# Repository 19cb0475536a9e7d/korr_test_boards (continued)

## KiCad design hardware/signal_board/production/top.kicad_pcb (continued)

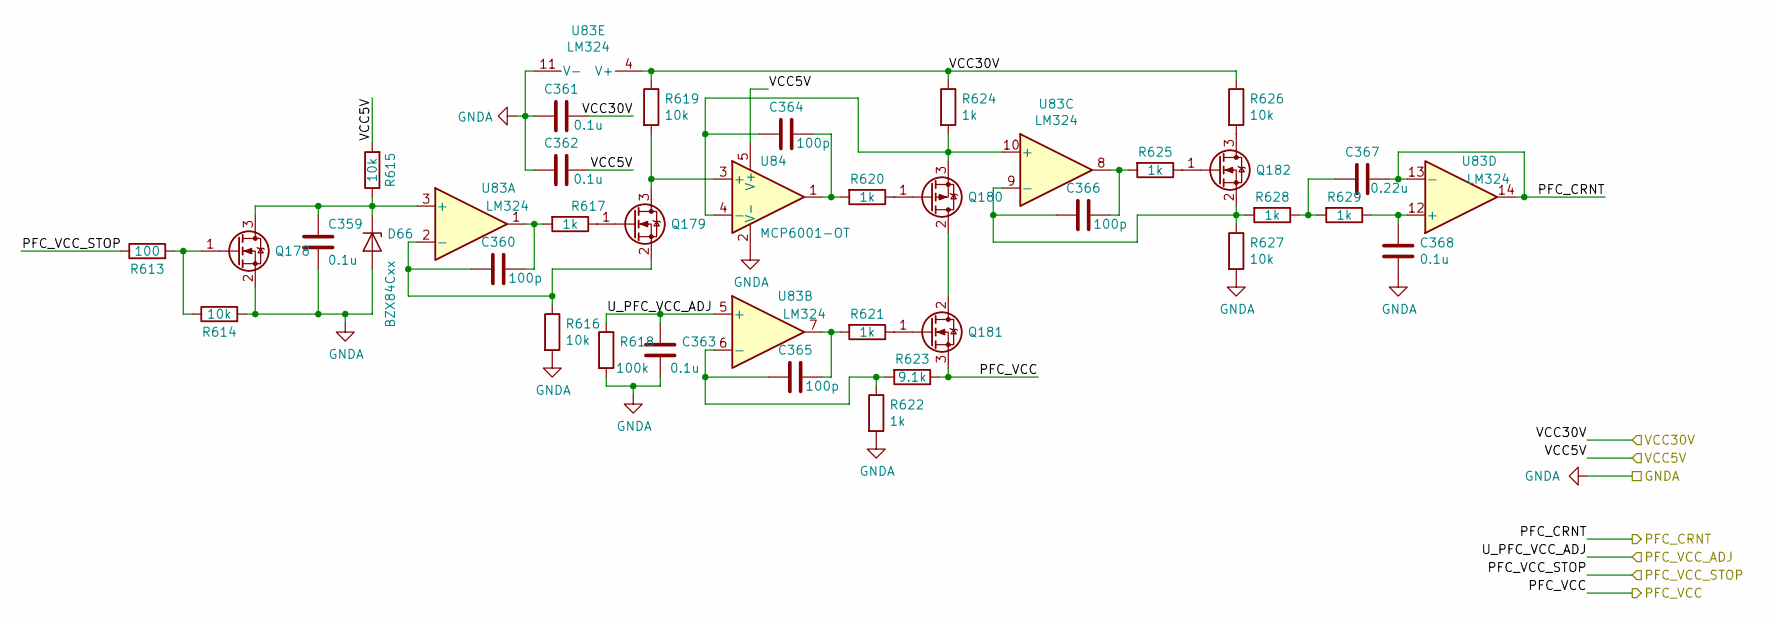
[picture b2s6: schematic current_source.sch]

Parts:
C12, C14, C15, C16, C21: 0.1u; C_0603_1608Metric
C13, C17, C18, C19: 100p; C_0603_1608Metric
C20: 0.22u; C_0603_1608Metric
D2: BZX84Cxx; D_SOT-23_ANK
Q8, Q9, Q12: Q_NMOS_GSD; SOT-23
Q10: Q_PMOS_GDS; TO-252-2
Q11: Q_NMOS_GDS; TO-252-2
R24: 100; R_0603_1608Metric
R25, R26, R27, R30, R37, R38: 10k; R_0603_1608Metric
R28, R31, R32, R33, R36, R39, R40: 1k; R_0603_1608Metric
R29: 100k; R_0603_1608Metric
R34: 9.1k; R_0603_1608Metric
R35: 1k; R_1206_3216Metric
U4: LM324; SOIC-14_3.9x8.7mm_P1.27mm
U5: MCP6001-OT; SOT-23-5

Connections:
/Cell_0_Sheet/CurrentSource_A_Sheet/PFC_CRNT: C20.1, U4.13 (-), U4.14; also elsewhere on the board
/PFC_STOP_0: R24.1; also elsewhere on the board
/PFC_VCC_DUT_0: Q11.3 (S), R34.1; also elsewhere on the board
/U_PFC_VCC_ADJ: C16.1, R29.1, U4.5 (+); also elsewhere on the board
/VCC5V: C15.1, R26.2, U5.5 (V+); also elsewhere on the board
/VCC30V: C14.1, R30.1, R35.1, R37.1, U4.4 (V+); also elsewhere on the board
GNDA: C12.2, C14.2, C15.2, C16.2, C21.2, D2.2 (A), Q8.2 (S), R25.2, R27.2, R29.2, R33.2, R38.2, U4.11 (V-), U5.2 (V-); also elsewhere on the board
unnamed: C12.1, D2.1 (K), Q8.3 (D), R26.1, U4.3 (+)
unnamed: C13.1, R28.2, U4.1
unnamed: C13.2, Q9.2 (S), R27.1, U4.2 (-)
unnamed: C17.1, R31.2, U5.1
unnamed: C17.2, Q10.3 (S), R35.2, U4.10 (+), U5.4 (-)
unnamed: C18.1, R32.2, U4.7
unnamed: C18.2, R33.1, R34.2, U4.6 (-)
unnamed: C19.1, R36.2, U4.8
unnamed: C19.2, Q12.2 (S), R38.1, R39.2, U4.9 (-)
unnamed: C20.2, R39.1, R40.2
unnamed: C21.1, R40.1, U4.12 (+)
unnamed: Q8.1 (G), R24.2, R25.1
unnamed: Q9.1 (G), R28.1
unnamed: Q9.3 (D), R30.2, U5.3 (+)
unnamed: Q10.1 (G), R31.1
unnamed: Q10.2 (D), Q11.2 (D)
unnamed: Q11.1 (G), R32.1
unnamed: Q12.1 (G), R36.1
unnamed: Q12.3 (D), R37.2

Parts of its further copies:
C2, C4, C5, C6, C11, C39, C41, C42, C43, C48, C49, C51, C52, C53, C58, C63, C65, C66, C67, C72, C73, C109, C110, C111, C116, C118, C120, C121, C122, C127, C128, C130, C131, C132, C137, C139, C141, C142, C143, C148, C149, C151, C152, C153, C158, C160, C162, C163, C164, C169, C170, C172, C173, C174, C179, C181, C183, C184, C185, C190, C191, C193, C194, C195, C200, C202, C204, C205, C206, C211, C212, C214, C215, C216, C221, C223, C225, C226, C227, C232, C233, C235, C236, C237, C242, C244, C246, C247, C248, C253, C254, C256, C257, C258, C263, C265, C267, C268, C269, C274, C275, C277, C278, C279, C284, C286, C288, C289, C290, C295, C296, C298, C299, C300, C305, C307, C309, C310, C311, C316, C317, C319, C320, C321, C326, C328, C330, C331, C332, C337, C338, C340, C341, C342, C347, C349, C351, C352, C353, C358, C359, C361, C362, C363, C368: 0.1u; C_0603_1608Metric
C3, C7, C8, C9, C40, C44, C45, C46, C50, C54, C55, C56, C64, C68, C69, C70, C108, C112, C113, C114, C119, C123, C124, C125, C129, C133, C134, C135, C140, C144, C145, C146, C150, C154, C155, C156, C161, C165, C166, C167, C171, C175, C176, C177, C182, C186, C187, C188, C192, C196, C197, C198, C203, C207, C208, C209, C213, C217, C218, C219, C224, C228, C229, C230, C234, C238, C239, C240, C245, C249, C250, C251, C255, C259, C260, C261, C266, C270, C271, C272, C276, C280, C281, C282, C287, C291, C292, C293, C297, C301, C302, C303, C308, C312, C313, C314, C318, C322, C323, C324, C329, C333, C334, C335, C339, C343, C344, C345, C350, C354, C355, C356, C360, C364, C365, C366: 100p; C_0603_1608Metric
C10, C47, C57, C71, C115, C126, C136, C147, C157, C168, C178, C189, C199, C210, C220, C231, C241, C252, C262, C273, C283, C294, C304, C315, C325, C336, C346, C357, C367: 0.22u; C_0603_1608Metric
D1, D5, D6, D41, D42, D43, D44, D45, D46, D47, D48, D49, D50, D51, D52, D53, D54, D55, D56, D57, D58, D59, D60, D61, D62, D63, D64, D65, D66: BZX84Cxx; D_SOT-23_ANK
Q3, Q4, Q7, Q16, Q17, Q20, Q21, Q22, Q25, Q29, Q30, Q33, Q34, Q35, Q38, Q41, Q42, Q45, Q46, Q47, Q50, Q53, Q54, Q57, Q58, Q59, Q62, Q65, Q66, Q69, Q70, Q71, Q74, Q77, Q78, Q81, Q82, Q83, Q86, Q89, Q90, Q93, Q94, Q95, Q98, Q101, Q102, Q105, Q106, Q107, Q110, Q113, Q114, Q117, Q118, Q119, Q122, Q125, Q126, Q129, Q130, Q131, Q134, Q137, Q138, Q141, Q142, Q143, Q146, Q149, Q150, Q153, Q154, Q155, Q158, Q161, Q162, Q165, Q166, Q167, Q170, Q173, Q174, Q177, Q178, Q179, Q182: Q_NMOS_GSD; SOT-23
Q5, Q18, Q23, Q31, Q36, Q43, Q48, Q55, Q60, Q67, Q72, Q79, Q84, Q91, Q96, Q103, Q108, Q115, Q120, Q127, Q132, Q139, Q144, Q151, Q156, Q163, Q168, Q175, Q180: Q_PMOS_GDS; TO-252-2
Q6, Q19, Q24, Q32, Q37, Q44, Q49, Q56, Q61, Q68, Q73, Q80, Q85, Q92, Q97, Q104, Q109, Q116, Q121, Q128, Q133, Q140, Q145, Q152, Q157, Q164, Q169, Q176, Q181: Q_NMOS_GDS; TO-252-2
R7, R59, R76, R106, R133, R156, R173, R196, R213, R236, R253, R276, R293, R316, R333, R356, R373, R396, R413, R436, R453, R476, R493, R516, R533, R556, R573, R596, R613: 100; R_0603_1608Metric
R8, R9, R10, R13, R20, R21, R60, R61, R62, R65, R72, R73, R77, R78, R79, R82, R89, R90, R107, R118, R119, R122, R129, R130, R134, R135, R136, R139, R146, R147, R157, R158, R159, R162, R169, R170, R174, R175, R176, R179, R186, R187, R197, R198, R199, R202, R209, R210, R214, R215, R216, R219, R226, R227, R237, R238, R239, R242, R249, R250, R254, R255, R256, R259, R266, R267, R277, R278, R279, R282, R289, R290, R294, R295, R296, R299, R306, R307, R317, R318, R319, R322, R329, R330, R334, R335, R336, R339, R346, R347, R357, R358, R359, R362, R369, R370, R374, R375, R376, R379, R386, R387, R397, R398, R399, R402, R409, R410, R414, R415, R416, R419, R426, R427, R437, R438, R439, R442, R449, R450, R454, R455, R456, R459, R466, R467, R477, R478, R479, R482, R489, R490, R494, R495, R496, R499, R506, R507, R517, R518, R519, R522, R529, R530, R534, R535, R536, R539, R546, R547, R557, R558, R559, R562, R569, R570, R574, R575, R576, R579, R586, R587, R597, R598, R599, R602, R609, R610, R614, R615, R616, R619, R626, R627: 10k; R_0603_1608Metric
R11, R14, R15, R16, R19, R22, R23, R63, R66, R67, R68, R71, R74, R75, R80, R83, R84, R85, R88, R91, R92, R120, R123, R124, R125, R128, R131, R132, R137, R140, R141, R142, R145, R148, R149, R160, R163, R164, R165, R168, R171, R172, R177, R180, R181, R182, R185, R188, R189, R200, R203, R204, R205, R208, R211, R212, R217, R220, R221, R222, R225, R228, R229, R240, R243, R244, R245, R248, R251, R252, R257, R260, R261, R262, R265, R268, R269, R280, R283, R284, R285, R288, R291, R292, R297, R300, R301, R302, R305, R308, R309, R320, R323, R324, R325, R328, R331, R332, R337, R340, R341, R342, R345, R348, R349, R360, R363, R364, R365, R368, R371, R372, R377, R380, R381, R382, R385, R388, R389, R400, R403, R404, R405, R408, R411, R412, R417, R420, R421, R422, R425, R428, R429, R440, R443, R444, R445, R448, R451, R452, R457, R460, R461, R462, R465, R468, R469, R480, R483, R484, R485, R488, R491, R492, R497, R500, R501, R502, R505, R508, R509, R520, R523, R524, R525, R528, R531, R532, R537, R540, R541, R542, R545, R548, R549, R560, R563, R564, R565, R568, R571, R572, R577, R580, R581, R582, R585, R588, R589, R600, R603, R604, R605, R608, R611, R612, R617, R620, R621, R622, R625, R628, R629: 1k; R_0603_1608Metric
R12, R64, R81, R121, R138, R161, R178, R201, R218, R241, R258, R281, R298, R321, R338, R361, R378, R401, R418, R441, R458, R481, R498, R521, R538, R561, R578, R601, R618: 100k; R_0603_1608Metric
R17, R69, R86, R126, R143, R166, R183, R206, R223, R246, R263, R286, R303, R326, R343, R366, R383, R406, R423, R446, R463, R486, R503, R526, R543, R566, R583, R606, R623: 9.1k; R_0603_1608Metric
R18, R70, R87, R127, R144, R167, R184, R207, R224, R247, R264, R287, R304, R327, R344, R367, R384, R407, R424, R447, R464, R487, R504, R527, R544, R567, R584, R607, R624: 1k; R_1206_3216Metric
U2, U11, U13, U17, U19, U26, U28, U31, U33, U36, U38, U41, U43, U46, U48, U51, U53, U56, U58, U61, U63, U66, U68, U71, U73, U76, U78, U81, U83: LM324; SOIC-14_3.9x8.7mm_P1.27mm
U3, U12, U14, U18, U24, U27, U29, U32, U34, U37, U39, U42, U44, U47, U49, U52, U54, U57, U59, U62, U64, U67, U69, U72, U74, U77, U79, U82, U84: MCP6001-OT; SOT-23-5

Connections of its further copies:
/Cell_0_Sheet/CurrentSource_B_Sheet/PFC_CRNT: C10.1, U2.13 (-), U2.14; also elsewhere on the board
/Cell_1_Sheet/CurrentSource_A_Sheet/PFC_CRNT: C57.1, U13.13 (-), U13.14; also elsewhere on the board
/Cell_1_Sheet/CurrentSource_B_Sheet/PFC_CRNT: C47.1, U11.13 (-), U11.14; also elsewhere on the board
/Cell_2_Sheet/CurrentSource_A_Sheet/PFC_CRNT: C115.1, U19.13 (-), U19.14; also elsewhere on the board
/Cell_2_Sheet/CurrentSource_B_Sheet/PFC_CRNT: C71.1, U17.13 (-), U17.14; also elsewhere on the board
/Cell_3_Sheet/CurrentSource_A_Sheet/PFC_CRNT: C136.1, U28.13 (-), U28.14; also elsewhere on the board
/Cell_3_Sheet/CurrentSource_B_Sheet/PFC_CRNT: C126.1, U26.13 (-), U26.14; also elsewhere on the board
/PFC_STOP_1: R7.1; also elsewhere on the board
/PFC_STOP_2: R76.1; also elsewhere on the board
/PFC_STOP_3: R59.1; also elsewhere on the board
/PFC_STOP_4: R133.1; also elsewhere on the board
/PFC_STOP_5: R106.1; also elsewhere on the board
/PFC_STOP_6: R173.1; also elsewhere on the board
/PFC_STOP_7: R156.1; also elsewhere on the board
/PFC_STOP_8: R213.1; also elsewhere on the board
/PFC_STOP_9: R196.1; also elsewhere on the board
/PFC_STOP_10: R253.1; also elsewhere on the board
/PFC_STOP_11: R236.1; also elsewhere on the board
/PFC_STOP_12: R293.1; also elsewhere on the board
/PFC_STOP_13: R276.1; also elsewhere on the board
/PFC_STOP_14: R333.1; also elsewhere on the board
/PFC_STOP_15: R316.1; also elsewhere on the board
/PFC_STOP_16: R373.1; also elsewhere on the board
/PFC_STOP_17: R356.1; also elsewhere on the board
/PFC_STOP_18: R413.1; also elsewhere on the board
/PFC_STOP_19: R396.1; also elsewhere on the board
/PFC_STOP_20: R453.1; also elsewhere on the board
/PFC_STOP_21: R436.1; also elsewhere on the board
/PFC_STOP_22: R493.1; also elsewhere on the board
/PFC_STOP_23: R476.1; also elsewhere on the board
/PFC_STOP_24: R533.1; also elsewhere on the board
/PFC_STOP_25: R516.1; also elsewhere on the board
/PFC_STOP_26: R573.1; also elsewhere on the board
/PFC_STOP_27: R556.1; also elsewhere on the board
/PFC_STOP_28: R613.1; also elsewhere on the board
/PFC_STOP_29: R596.1; also elsewhere on the board
/PFC_VCC_DUT_1: Q6.3 (S), R17.1; also elsewhere on the board
/PFC_VCC_DUT_2: Q24.3 (S), R86.1; also elsewhere on the board
/PFC_VCC_DUT_3: Q19.3 (S), R69.1; also elsewhere on the board
/PFC_VCC_DUT_4: Q37.3 (S), R143.1; also elsewhere on the board
/PFC_VCC_DUT_5: Q32.3 (S), R126.1; also elsewhere on the board
/PFC_VCC_DUT_6: Q49.3 (S), R183.1; also elsewhere on the board
/PFC_VCC_DUT_7: Q44.3 (S), R166.1; also elsewhere on the board
/PFC_VCC_DUT_8: Q61.3 (S), R223.1; also elsewhere on the board
/PFC_VCC_DUT_9: Q56.3 (S), R206.1; also elsewhere on the board
/PFC_VCC_DUT_10: Q73.3 (S), R263.1; also elsewhere on the board
/PFC_VCC_DUT_11: Q68.3 (S), R246.1; also elsewhere on the board
/PFC_VCC_DUT_12: Q85.3 (S), R303.1; also elsewhere on the board
/PFC_VCC_DUT_13: Q80.3 (S), R286.1; also elsewhere on the board
/PFC_VCC_DUT_14: Q97.3 (S), R343.1; also elsewhere on the board
/PFC_VCC_DUT_15: Q92.3 (S), R326.1; also elsewhere on the board
/PFC_VCC_DUT_16: Q109.3 (S), R383.1; also elsewhere on the board
/PFC_VCC_DUT_17: Q104.3 (S), R366.1; also elsewhere on the board
/PFC_VCC_DUT_18: Q121.3 (S), R423.1; also elsewhere on the board
/PFC_VCC_DUT_19: Q116.3 (S), R406.1; also elsewhere on the board
/PFC_VCC_DUT_20: Q133.3 (S), R463.1; also elsewhere on the board
/PFC_VCC_DUT_21: Q128.3 (S), R446.1; also elsewhere on the board
/PFC_VCC_DUT_22: Q145.3 (S), R503.1; also elsewhere on the board
/PFC_VCC_DUT_23: Q140.3 (S), R486.1; also elsewhere on the board
/PFC_VCC_DUT_24: Q157.3 (S), R543.1; also elsewhere on the board
/PFC_VCC_DUT_25: Q152.3 (S), R526.1; also elsewhere on the board
/PFC_VCC_DUT_26: Q169.3 (S), R583.1; also elsewhere on the board
/PFC_VCC_DUT_27: Q164.3 (S), R566.1; also elsewhere on the board
/PFC_VCC_DUT_28: Q181.3 (S), R623.1; also elsewhere on the board
/PFC_VCC_DUT_29: Q176.3 (S), R606.1; also elsewhere on the board
/U_PFC_VCC_ADJ: C6.1, C43.1, C53.1, C67.1, C111.1, C122.1, C132.1, C143.1, C153.1, C164.1, C174.1, C185.1, C195.1, C206.1, C216.1, C227.1, C237.1, C248.1, C258.1, C269.1, C279.1, C290.1, C300.1, C311.1, C321.1, C332.1, C342.1, C353.1, C363.1, R12.1, R64.1, R81.1, R121.1, R138.1, R161.1, R178.1, R201.1, R218.1, R241.1, R258.1, R281.1, R298.1, R321.1, R338.1, R361.1, R378.1, R401.1, R418.1, R441.1, R458.1, R481.1, R498.1, R521.1, R538.1, R561.1, R578.1, R601.1, R618.1, U2.5 (+), U11.5 (+), U13.5 (+), U17.5 (+), U19.5 (+), U26.5 (+), U28.5 (+), U31.5 (+), U33.5 (+), U36.5 (+), U38.5 (+), U41.5 (+), U43.5 (+), U46.5 (+), U48.5 (+), U51.5 (+), U53.5 (+), U56.5 (+), U58.5 (+), U61.5 (+), U63.5 (+), U66.5 (+), U68.5 (+), U71.5 (+), U73.5 (+), U76.5 (+), U78.5 (+), U81.5 (+), U83.5 (+); also elsewhere on the board
/VCC5V: C5.1, C42.1, C52.1, C66.1, C110.1, C121.1, C131.1, C142.1, C152.1, C163.1, C173.1, C184.1, C194.1, C205.1, C215.1, C226.1, C236.1, C247.1, C257.1, C268.1, C278.1, C289.1, C299.1, C310.1, C320.1, C331.1, C341.1, C352.1, C362.1, R9.2, R61.2, R78.2, R118.2, R135.2, R158.2, R175.2, R198.2, R215.2, R238.2, R255.2, R278.2, R295.2, R318.2, R335.2, R358.2, R375.2, R398.2, R415.2, R438.2, R455.2, R478.2, R495.2, R518.2, R535.2, R558.2, R575.2, R598.2, R615.2, U3.5 (V+), U12.5 (V+), U14.5 (V+), U18.5 (V+), U24.5 (V+), U27.5 (V+), U29.5 (V+), U32.5 (V+), U34.5 (V+), U37.5 (V+), U39.5 (V+), U42.5 (V+), U44.5 (V+), U47.5 (V+), U49.5 (V+), U52.5 (V+), U54.5 (V+), U57.5 (V+), U59.5 (V+), U62.5 (V+), U64.5 (V+), U67.5 (V+), U69.5 (V+), U72.5 (V+), U74.5 (V+), U77.5 (V+), U79.5 (V+), U82.5 (V+), U84.5 (V+); also elsewhere on the board
/VCC30V: C4.1, C41.1, C51.1, C65.1, C109.1, C120.1, C130.1, C141.1, C151.1, C162.1, C172.1, C183.1, C193.1, C204.1, C214.1, C225.1, C235.1, C246.1, C256.1, C267.1, C277.1, C288.1, C298.1, C309.1, C319.1, C330.1, C340.1, C351.1, C361.1, R13.1, R18.1, R20.1, R65.1, R70.1, R72.1, R82.1, R87.1, R89.1, R122.1, R127.1, R129.1, R139.1, R144.1, R146.1, R162.1, R167.1, R169.1, R179.1, R184.1, R186.1, R202.1, R207.1, R209.1, R219.1, R224.1, R226.1, R242.1, R247.1, R249.1, R259.1, R264.1, R266.1, R282.1, R287.1, R289.1, R299.1, R304.1, R306.1, R322.1, R327.1, R329.1, R339.1, R344.1, R346.1, R362.1, R367.1, R369.1, R379.1, R384.1, R386.1, R402.1, R407.1, R409.1, R419.1, R424.1, R426.1, R442.1, R447.1, R449.1, R459.1, R464.1, R466.1, R482.1, R487.1, R489.1, R499.1, R504.1, R506.1, R522.1, R527.1, R529.1, R539.1, R544.1, R546.1, R562.1, R567.1, R569.1, R579.1, R584.1, R586.1, R602.1, R607.1, R609.1, R619.1, R624.1, R626.1, U2.4 (V+), U11.4 (V+), U13.4 (V+), U17.4 (V+), U19.4 (V+), U26.4 (V+), U28.4 (V+), U31.4 (V+), U33.4 (V+), U36.4 (V+), U38.4 (V+), U41.4 (V+), U43.4 (V+), U46.4 (V+), U48.4 (V+), U51.4 (V+), U53.4 (V+), U56.4 (V+), U58.4 (V+), U61.4 (V+), U63.4 (V+), U66.4 (V+), U68.4 (V+), U71.4 (V+), U73.4 (V+), U76.4 (V+), U78.4 (V+), U81.4 (V+), U83.4 (V+); also elsewhere on the board
/sheet5E9AFF1E/CurrentSource_A_Sheet/PFC_CRNT: C283.1, U63.13 (-), U63.14; also elsewhere on the board
/sheet5E9AFF1E/CurrentSource_B_Sheet/PFC_CRNT: C273.1, U61.13 (-), U61.14; also elsewhere on the board
/sheet5E9AFF1F/CurrentSource_A_Sheet/PFC_CRNT: C304.1, U68.13 (-), U68.14; also elsewhere on the board
/sheet5E9AFF1F/CurrentSource_B_Sheet/PFC_CRNT: C294.1, U66.13 (-), U66.14; also elsewhere on the board
/sheet5E9AFF20/CurrentSource_A_Sheet/PFC_CRNT: C325.1, U73.13 (-), U73.14; also elsewhere on the board
/sheet5E9AFF20/CurrentSource_B_Sheet/PFC_CRNT: C315.1, U71.13 (-), U71.14; also elsewhere on the board
/sheet5E9AFF21/CurrentSource_A_Sheet/PFC_CRNT: C346.1, U78.13 (-), U78.14; also elsewhere on the board
/sheet5E9AFF21/CurrentSource_B_Sheet/PFC_CRNT: C336.1, U76.13 (-), U76.14; also elsewhere on the board
/sheet5E9AFF22/CurrentSource_A_Sheet/PFC_CRNT: C367.1, U83.13 (-), U83.14; also elsewhere on the board
/sheet5E9AFF22/CurrentSource_B_Sheet/PFC_CRNT: C357.1, U81.13 (-), U81.14; also elsewhere on the board
/sheet5E8790F9/CurrentSource_A_Sheet/PFC_CRNT: C157.1, U33.13 (-), U33.14; also elsewhere on the board
/sheet5E8790F9/CurrentSource_B_Sheet/PFC_CRNT: C147.1, U31.13 (-), U31.14; also elsewhere on the board
/sheet5E9528FB/CurrentSource_A_Sheet/PFC_CRNT: C178.1, U38.13 (-), U38.14; also elsewhere on the board
/sheet5E9528FB/CurrentSource_B_Sheet/PFC_CRNT: C168.1, U36.13 (-), U36.14; also elsewhere on the board
/sheet5E9528FC/CurrentSource_A_Sheet/PFC_CRNT: C199.1, U43.13 (-), U43.14; also elsewhere on the board
/sheet5E9528FC/CurrentSource_B_Sheet/PFC_CRNT: C189.1, U41.13 (-), U41.14; also elsewhere on the board
/sheet5E9528FD/CurrentSource_A_Sheet/PFC_CRNT: C220.1, U48.13 (-), U48.14; also elsewhere on the board
/sheet5E9528FD/CurrentSource_B_Sheet/PFC_CRNT: C210.1, U46.13 (-), U46.14; also elsewhere on the board
/sheet5E9528FE/CurrentSource_A_Sheet/PFC_CRNT: C241.1, U53.13 (-), U53.14; also elsewhere on the board
/sheet5E9528FE/CurrentSource_B_Sheet/PFC_CRNT: C231.1, U51.13 (-), U51.14; also elsewhere on the board
/sheet5E9528FF/CurrentSource_A_Sheet/PFC_CRNT: C262.1, U58.13 (-), U58.14; also elsewhere on the board
/sheet5E9528FF/CurrentSource_B_Sheet/PFC_CRNT: C252.1, U56.13 (-), U56.14; also elsewhere on the board
GNDA: C2.2, C4.2, C5.2, C6.2, C11.2, C39.2, C41.2, C42.2, C43.2, C48.2, C49.2, C51.2, C52.2, C53.2, C58.2, C63.2, C65.2, C66.2, C67.2, C72.2, C73.2, C109.2, C110.2, C111.2, C116.2, C118.2, C120.2, C121.2, C122.2, C127.2, C128.2, C130.2, C131.2, C132.2, C137.2, C139.2, C141.2, C142.2, C143.2, C148.2, C149.2, C151.2, C152.2, C153.2, C158.2, C160.2, C162.2, C163.2, C164.2, C169.2, C170.2, C172.2, C173.2, C174.2, C179.2, C181.2, C183.2, C184.2, C185.2, C190.2, C191.2, C193.2, C194.2, C195.2, C200.2, C202.2, C204.2, C205.2, C206.2, C211.2, C212.2, C214.2, C215.2, C216.2, C221.2, C223.2, C225.2, C226.2, C227.2, C232.2, C233.2, C235.2, C236.2, C237.2, C242.2, C244.2, C246.2, C247.2, C248.2, C253.2, C254.2, C256.2, C257.2, C258.2, C263.2, C265.2, C267.2, C268.2, C269.2, C274.2, C275.2, C277.2, C278.2, C279.2, C284.2, C286.2, C288.2, C289.2, C290.2, C295.2, C296.2, C298.2, C299.2, C300.2, C305.2, C307.2, C309.2, C310.2, C311.2, C316.2, C317.2, C319.2, C320.2, C321.2, C326.2, C328.2, C330.2, C331.2, C332.2, C337.2, C338.2, C340.2, C341.2, C342.2, C347.2, C349.2, C351.2, C352.2, C353.2, C358.2, C359.2, C361.2, C362.2, C363.2, C368.2, D1.2 (A), D5.2 (A), D6.2 (A), D41.2 (A), D42.2 (A), D43.2 (A), D44.2 (A), D45.2 (A), D46.2 (A), D47.2 (A), D48.2 (A), D49.2 (A), D50.2 (A), D51.2 (A), D52.2 (A), D53.2 (A), D54.2 (A), D55.2 (A), D56.2 (A), D57.2 (A), D58.2 (A), D59.2 (A), D60.2 (A), D61.2 (A), D62.2 (A), D63.2 (A), D64.2 (A), D65.2 (A), D66.2 (A), Q3.2 (S), Q16.2 (S), Q21.2 (S), Q29.2 (S), Q34.2 (S), Q41.2 (S), Q46.2 (S), Q53.2 (S), Q58.2 (S), Q65.2 (S), Q70.2 (S), Q77.2 (S), Q82.2 (S), Q89.2 (S), Q94.2 (S), Q101.2 (S), Q106.2 (S), Q113.2 (S), Q118.2 (S), Q125.2 (S), Q130.2 (S), Q137.2 (S), Q142.2 (S), Q149.2 (S), Q154.2 (S), Q161.2 (S), Q166.2 (S), Q173.2 (S), Q178.2 (S), R8.2, R10.2, R12.2, R16.2, R21.2, R60.2, R62.2, R64.2, R68.2, R73.2, R77.2, R79.2, R81.2, R85.2, R90.2, R107.2, R119.2, R121.2, R125.2, R130.2, R134.2, R136.2, R138.2, R142.2, R147.2, R157.2, R159.2, R161.2, R165.2, R170.2, R174.2, R176.2, R178.2, R182.2, R187.2, R197.2, R199.2, R201.2, R205.2, R210.2, R214.2, R216.2, R218.2, R222.2, R227.2, R237.2, R239.2, R241.2, R245.2, R250.2, R254.2, R256.2, R258.2, R262.2, R267.2, R277.2, R279.2, R281.2, R285.2, R290.2, R294.2, R296.2, R298.2, R302.2, R307.2, R317.2, R319.2, R321.2, R325.2, R330.2, R334.2, R336.2, R338.2, R342.2, R347.2, R357.2, R359.2, R361.2, R365.2, R370.2, R374.2, R376.2, R378.2, R382.2, R387.2, R397.2, R399.2, R401.2, R405.2, R410.2, R414.2, R416.2, R418.2, R422.2, R427.2, R437.2, R439.2, R441.2, R445.2, R450.2, R454.2, R456.2, R458.2, R462.2, R467.2, R477.2, R479.2, R481.2, R485.2, R490.2, R494.2, R496.2, R498.2, R502.2, R507.2, R517.2, R519.2, R521.2, R525.2, R530.2, R534.2, R536.2, R538.2, R542.2, R547.2, R557.2, R559.2, R561.2, R565.2, R570.2, R574.2, R576.2, R578.2, R582.2, R587.2, R597.2, R599.2, R601.2, R605.2, R610.2, R614.2, R616.2, R618.2, R622.2, R627.2, U2.11 (V-), U3.2 (V-), U11.11 (V-), U12.2 (V-), U13.11 (V-), U14.2 (V-), U17.11 (V-), U18.2 (V-), U19.11 (V-), U24.2 (V-), U26.11 (V-), U27.2 (V-), U28.11 (V-), U29.2 (V-), U31.11 (V-), U32.2 (V-), U33.11 (V-), U34.2 (V-), U36.11 (V-), U37.2 (V-), U38.11 (V-), U39.2 (V-), U41.11 (V-), U42.2 (V-), U43.11 (V-), U44.2 (V-), U46.11 (V-), U47.2 (V-), U48.11 (V-), U49.2 (V-), U51.11 (V-), U52.2 (V-), U53.11 (V-), U54.2 (V-), U56.11 (V-), U57.2 (V-), U58.11 (V-), U59.2 (V-), U61.11 (V-), U62.2 (V-), U63.11 (V-), U64.2 (V-), U66.11 (V-), U67.2 (V-), U68.11 (V-), U69.2 (V-), U71.11 (V-), U72.2 (V-), U73.11 (V-), U74.2 (V-), U76.11 (V-), U77.2 (V-), U78.11 (V-), U79.2 (V-), U81.11 (V-), U82.2 (V-), U83.11 (V-), U84.2 (V-); also elsewhere on the board
unnamed: C2.1, D1.1 (K), Q3.3 (D), R9.1, U2.3 (+)
unnamed: C3.1, R11.2, U2.1
unnamed: C3.2, Q4.2 (S), R10.1, U2.2 (-)
unnamed: C7.1, R14.2, U3.1
unnamed: C7.2, Q5.3 (S), R18.2, U2.10 (+), U3.4 (-)
unnamed: C8.1, R15.2, U2.7
unnamed: C8.2, R16.1, R17.2, U2.6 (-)
unnamed: C9.1, R19.2, U2.8
unnamed: C9.2, Q7.2 (S), R21.1, R22.2, U2.9 (-)
unnamed: C10.2, R22.1, R23.2
unnamed: C11.1, R23.1, U2.12 (+)
unnamed: C39.1, D5.1 (K), Q16.3 (D), R61.1, U11.3 (+)
unnamed: C40.1, R63.2, U11.1
unnamed: C40.2, Q17.2 (S), R62.1, U11.2 (-)
unnamed: C44.1, R66.2, U12.1
unnamed: C44.2, Q18.3 (S), R70.2, U11.10 (+), U12.4 (-)
unnamed: C45.1, R67.2, U11.7
unnamed: C45.2, R68.1, R69.2, U11.6 (-)
unnamed: C46.1, R71.2, U11.8
unnamed: C46.2, Q20.2 (S), R73.1, R74.2, U11.9 (-)
unnamed: C47.2, R74.1, R75.2
unnamed: C48.1, R75.1, U11.12 (+)
unnamed: C49.1, D6.1 (K), Q21.3 (D), R78.1, U13.3 (+)
unnamed: C50.1, R80.2, U13.1
unnamed: C50.2, Q22.2 (S), R79.1, U13.2 (-)
unnamed: C54.1, R83.2, U14.1
unnamed: C54.2, Q23.3 (S), R87.2, U13.10 (+), U14.4 (-)
unnamed: C55.1, R84.2, U13.7
unnamed: C55.2, R85.1, R86.2, U13.6 (-)
unnamed: C56.1, R88.2, U13.8
unnamed: C56.2, Q25.2 (S), R90.1, R91.2, U13.9 (-)
unnamed: C57.2, R91.1, R92.2
unnamed: C58.1, R92.1, U13.12 (+)
unnamed: C63.1, D41.1 (K), Q29.3 (D), R118.1, U17.3 (+)
unnamed: C64.1, R120.2, U17.1
unnamed: C64.2, Q30.2 (S), R119.1, U17.2 (-)
unnamed: C68.1, R123.2, U18.1
unnamed: C68.2, Q31.3 (S), R127.2, U17.10 (+), U18.4 (-)
unnamed: C69.1, R124.2, U17.7
unnamed: C69.2, R125.1, R126.2, U17.6 (-)
unnamed: C70.1, R128.2, U17.8
unnamed: C70.2, Q33.2 (S), R130.1, R131.2, U17.9 (-)
unnamed: C71.2, R131.1, R132.2
unnamed: C72.1, R132.1, U17.12 (+)
unnamed: C73.1, D42.1 (K), Q34.3 (D), R135.1, U19.3 (+)
unnamed: C108.1, R137.2, U19.1
unnamed: C108.2, Q35.2 (S), R136.1, U19.2 (-)
unnamed: C112.1, R140.2, U24.1
unnamed: C112.2, Q36.3 (S), R144.2, U19.10 (+), U24.4 (-)
unnamed: C113.1, R141.2, U19.7
unnamed: C113.2, R142.1, R143.2, U19.6 (-)
unnamed: C114.1, R145.2, U19.8
unnamed: C114.2, Q38.2 (S), R147.1, R148.2, U19.9 (-)
unnamed: C115.2, R148.1, R149.2
unnamed: C116.1, R149.1, U19.12 (+)
unnamed: C118.1, D43.1 (K), Q41.3 (D), R158.1, U26.3 (+)
unnamed: C119.1, R160.2, U26.1
unnamed: C119.2, Q42.2 (S), R159.1, U26.2 (-)
unnamed: C123.1, R163.2, U27.1
unnamed: C123.2, Q43.3 (S), R167.2, U26.10 (+), U27.4 (-)
unnamed: C124.1, R164.2, U26.7
unnamed: C124.2, R165.1, R166.2, U26.6 (-)
unnamed: C125.1, R168.2, U26.8
unnamed: C125.2, Q45.2 (S), R170.1, R171.2, U26.9 (-)
unnamed: C126.2, R171.1, R172.2
unnamed: C127.1, R172.1, U26.12 (+)
unnamed: C128.1, D44.1 (K), Q46.3 (D), R175.1, U28.3 (+)
unnamed: C129.1, R177.2, U28.1
unnamed: C129.2, Q47.2 (S), R176.1, U28.2 (-)
unnamed: C133.1, R180.2, U29.1
unnamed: C133.2, Q48.3 (S), R184.2, U28.10 (+), U29.4 (-)
unnamed: C134.1, R181.2, U28.7
unnamed: C134.2, R182.1, R183.2, U28.6 (-)
unnamed: C135.1, R185.2, U28.8
unnamed: C135.2, Q50.2 (S), R187.1, R188.2, U28.9 (-)
unnamed: C136.2, R188.1, R189.2
unnamed: C137.1, R189.1, U28.12 (+)
unnamed: C139.1, D45.1 (K), Q53.3 (D), R198.1, U31.3 (+)
unnamed: C140.1, R200.2, U31.1
unnamed: C140.2, Q54.2 (S), R199.1, U31.2 (-)
unnamed: C144.1, R203.2, U32.1
unnamed: C144.2, Q55.3 (S), R207.2, U31.10 (+), U32.4 (-)
unnamed: C145.1, R204.2, U31.7
unnamed: C145.2, R205.1, R206.2, U31.6 (-)
unnamed: C146.1, R208.2, U31.8
unnamed: C146.2, Q57.2 (S), R210.1, R211.2, U31.9 (-)
unnamed: C147.2, R211.1, R212.2
unnamed: C148.1, R212.1, U31.12 (+)
unnamed: C149.1, D46.1 (K), Q58.3 (D), R215.1, U33.3 (+)
unnamed: C150.1, R217.2, U33.1
unnamed: C150.2, Q59.2 (S), R216.1, U33.2 (-)
unnamed: C154.1, R220.2, U34.1
unnamed: C154.2, Q60.3 (S), R224.2, U33.10 (+), U34.4 (-)
unnamed: C155.1, R221.2, U33.7
unnamed: C155.2, R222.1, R223.2, U33.6 (-)
unnamed: C156.1, R225.2, U33.8
unnamed: C156.2, Q62.2 (S), R227.1, R228.2, U33.9 (-)
unnamed: C157.2, R228.1, R229.2
unnamed: C158.1, R229.1, U33.12 (+)
unnamed: C160.1, D47.1 (K), Q65.3 (D), R238.1, U36.3 (+)
unnamed: C161.1, R240.2, U36.1
unnamed: C161.2, Q66.2 (S), R239.1, U36.2 (-)
unnamed: C165.1, R243.2, U37.1
unnamed: C165.2, Q67.3 (S), R247.2, U36.10 (+), U37.4 (-)
unnamed: C166.1, R244.2, U36.7
unnamed: C166.2, R245.1, R246.2, U36.6 (-)
unnamed: C167.1, R248.2, U36.8
unnamed: C167.2, Q69.2 (S), R250.1, R251.2, U36.9 (-)
unnamed: C168.2, R251.1, R252.2
unnamed: C169.1, R252.1, U36.12 (+)
unnamed: C170.1, D48.1 (K), Q70.3 (D), R255.1, U38.3 (+)
unnamed: C171.1, R257.2, U38.1
unnamed: C171.2, Q71.2 (S), R256.1, U38.2 (-)
unnamed: C175.1, R260.2, U39.1
unnamed: C175.2, Q72.3 (S), R264.2, U38.10 (+), U39.4 (-)
unnamed: C176.1, R261.2, U38.7
unnamed: C176.2, R262.1, R263.2, U38.6 (-)
unnamed: C177.1, R265.2, U38.8
unnamed: C177.2, Q74.2 (S), R267.1, R268.2, U38.9 (-)
unnamed: C178.2, R268.1, R269.2
unnamed: C179.1, R269.1, U38.12 (+)
unnamed: C181.1, D49.1 (K), Q77.3 (D), R278.1, U41.3 (+)
unnamed: C182.1, R280.2, U41.1
unnamed: C182.2, Q78.2 (S), R279.1, U41.2 (-)
unnamed: C186.1, R283.2, U42.1
unnamed: C186.2, Q79.3 (S), R287.2, U41.10 (+), U42.4 (-)
unnamed: C187.1, R284.2, U41.7
unnamed: C187.2, R285.1, R286.2, U41.6 (-)
unnamed: C188.1, R288.2, U41.8
unnamed: C188.2, Q81.2 (S), R290.1, R291.2, U41.9 (-)
unnamed: C189.2, R291.1, R292.2
unnamed: C190.1, R292.1, U41.12 (+)
unnamed: C191.1, D50.1 (K), Q82.3 (D), R295.1, U43.3 (+)
unnamed: C192.1, R297.2, U43.1
unnamed: C192.2, Q83.2 (S), R296.1, U43.2 (-)
unnamed: C196.1, R300.2, U44.1
unnamed: C196.2, Q84.3 (S), R304.2, U43.10 (+), U44.4 (-)
unnamed: C197.1, R301.2, U43.7
unnamed: C197.2, R302.1, R303.2, U43.6 (-)
unnamed: C198.1, R305.2, U43.8
unnamed: C198.2, Q86.2 (S), R307.1, R308.2, U43.9 (-)
unnamed: C199.2, R308.1, R309.2
unnamed: C200.1, R309.1, U43.12 (+)
unnamed: C202.1, D51.1 (K), Q89.3 (D), R318.1, U46.3 (+)
unnamed: C203.1, R320.2, U46.1
unnamed: C203.2, Q90.2 (S), R319.1, U46.2 (-)
unnamed: C207.1, R323.2, U47.1
unnamed: C207.2, Q91.3 (S), R327.2, U46.10 (+), U47.4 (-)
unnamed: C208.1, R324.2, U46.7
unnamed: C208.2, R325.1, R326.2, U46.6 (-)
unnamed: C209.1, R328.2, U46.8
unnamed: C209.2, Q93.2 (S), R330.1, R331.2, U46.9 (-)
unnamed: C210.2, R331.1, R332.2
unnamed: C211.1, R332.1, U46.12 (+)
unnamed: C212.1, D52.1 (K), Q94.3 (D), R335.1, U48.3 (+)
unnamed: C213.1, R337.2, U48.1
unnamed: C213.2, Q95.2 (S), R336.1, U48.2 (-)
unnamed: C217.1, R340.2, U49.1
unnamed: C217.2, Q96.3 (S), R344.2, U48.10 (+), U49.4 (-)
unnamed: C218.1, R341.2, U48.7
unnamed: C218.2, R342.1, R343.2, U48.6 (-)
unnamed: C219.1, R345.2, U48.8
unnamed: C219.2, Q98.2 (S), R347.1, R348.2, U48.9 (-)
unnamed: C220.2, R348.1, R349.2
unnamed: C221.1, R349.1, U48.12 (+)
unnamed: C223.1, D53.1 (K), Q101.3 (D), R358.1, U51.3 (+)
unnamed: C224.1, R360.2, U51.1
unnamed: C224.2, Q102.2 (S), R359.1, U51.2 (-)
unnamed: C228.1, R363.2, U52.1
unnamed: C228.2, Q103.3 (S), R367.2, U51.10 (+), U52.4 (-)
unnamed: C229.1, R364.2, U51.7
unnamed: C229.2, R365.1, R366.2, U51.6 (-)
unnamed: C230.1, R368.2, U51.8
unnamed: C230.2, Q105.2 (S), R370.1, R371.2, U51.9 (-)
unnamed: C231.2, R371.1, R372.2
unnamed: C232.1, R372.1, U51.12 (+)
unnamed: C233.1, D54.1 (K), Q106.3 (D), R375.1, U53.3 (+)
unnamed: C234.1, R377.2, U53.1
unnamed: C234.2, Q107.2 (S), R376.1, U53.2 (-)
unnamed: C238.1, R380.2, U54.1
unnamed: C238.2, Q108.3 (S), R384.2, U53.10 (+), U54.4 (-)
unnamed: C239.1, R381.2, U53.7
unnamed: C239.2, R382.1, R383.2, U53.6 (-)
unnamed: C240.1, R385.2, U53.8
unnamed: C240.2, Q110.2 (S), R387.1, R388.2, U53.9 (-)
unnamed: C241.2, R388.1, R389.2
unnamed: C242.1, R389.1, U53.12 (+)
unnamed: C244.1, D55.1 (K), Q113.3 (D), R398.1, U56.3 (+)
unnamed: C245.1, R400.2, U56.1
unnamed: C245.2, Q114.2 (S), R399.1, U56.2 (-)
unnamed: C249.1, R403.2, U57.1
unnamed: C249.2, Q115.3 (S), R407.2, U56.10 (+), U57.4 (-)
unnamed: C250.1, R404.2, U56.7
unnamed: C250.2, R405.1, R406.2, U56.6 (-)
unnamed: C251.1, R408.2, U56.8
unnamed: C251.2, Q117.2 (S), R410.1, R411.2, U56.9 (-)
unnamed: C252.2, R411.1, R412.2
unnamed: C253.1, R412.1, U56.12 (+)
unnamed: C254.1, D56.1 (K), Q118.3 (D), R415.1, U58.3 (+)
unnamed: C255.1, R417.2, U58.1
unnamed: C255.2, Q119.2 (S), R416.1, U58.2 (-)
unnamed: C259.1, R420.2, U59.1
unnamed: C259.2, Q120.3 (S), R424.2, U58.10 (+), U59.4 (-)
unnamed: C260.1, R421.2, U58.7
unnamed: C260.2, R422.1, R423.2, U58.6 (-)
unnamed: C261.1, R425.2, U58.8
unnamed: C261.2, Q122.2 (S), R427.1, R428.2, U58.9 (-)
unnamed: C262.2, R428.1, R429.2
unnamed: C263.1, R429.1, U58.12 (+)
unnamed: C265.1, D57.1 (K), Q125.3 (D), R438.1, U61.3 (+)
unnamed: C266.1, R440.2, U61.1
unnamed: C266.2, Q126.2 (S), R439.1, U61.2 (-)
unnamed: C270.1, R443.2, U62.1
unnamed: C270.2, Q127.3 (S), R447.2, U61.10 (+), U62.4 (-)
unnamed: C271.1, R444.2, U61.7
unnamed: C271.2, R445.1, R446.2, U61.6 (-)
unnamed: C272.1, R448.2, U61.8
unnamed: C272.2, Q129.2 (S), R450.1, R451.2, U61.9 (-)
unnamed: C273.2, R451.1, R452.2
unnamed: C274.1, R452.1, U61.12 (+)
unnamed: C275.1, D58.1 (K), Q130.3 (D), R455.1, U63.3 (+)
unnamed: C276.1, R457.2, U63.1
unnamed: C276.2, Q131.2 (S), R456.1, U63.2 (-)
unnamed: C280.1, R460.2, U64.1
unnamed: C280.2, Q132.3 (S), R464.2, U63.10 (+), U64.4 (-)
unnamed: C281.1, R461.2, U63.7
unnamed: C281.2, R462.1, R463.2, U63.6 (-)
unnamed: C282.1, R465.2, U63.8
unnamed: C282.2, Q134.2 (S), R467.1, R468.2, U63.9 (-)
unnamed: C283.2, R468.1, R469.2
unnamed: C284.1, R469.1, U63.12 (+)
unnamed: C286.1, D59.1 (K), Q137.3 (D), R478.1, U66.3 (+)
unnamed: C287.1, R480.2, U66.1
unnamed: C287.2, Q138.2 (S), R479.1, U66.2 (-)
unnamed: C291.1, R483.2, U67.1
unnamed: C291.2, Q139.3 (S), R487.2, U66.10 (+), U67.4 (-)
unnamed: C292.1, R484.2, U66.7
unnamed: C292.2, R485.1, R486.2, U66.6 (-)
unnamed: C293.1, R488.2, U66.8
unnamed: C293.2, Q141.2 (S), R490.1, R491.2, U66.9 (-)
unnamed: C294.2, R491.1, R492.2
unnamed: C295.1, R492.1, U66.12 (+)
unnamed: C296.1, D60.1 (K), Q142.3 (D), R495.1, U68.3 (+)
unnamed: C297.1, R497.2, U68.1
unnamed: C297.2, Q143.2 (S), R496.1, U68.2 (-)
unnamed: C301.1, R500.2, U69.1
unnamed: C301.2, Q144.3 (S), R504.2, U68.10 (+), U69.4 (-)
unnamed: C302.1, R501.2, U68.7
unnamed: C302.2, R502.1, R503.2, U68.6 (-)
unnamed: C303.1, R505.2, U68.8
unnamed: C303.2, Q146.2 (S), R507.1, R508.2, U68.9 (-)
unnamed: C304.2, R508.1, R509.2
unnamed: C305.1, R509.1, U68.12 (+)
unnamed: C307.1, D61.1 (K), Q149.3 (D), R518.1, U71.3 (+)
unnamed: C308.1, R520.2, U71.1
unnamed: C308.2, Q150.2 (S), R519.1, U71.2 (-)
unnamed: C312.1, R523.2, U72.1
unnamed: C312.2, Q151.3 (S), R527.2, U71.10 (+), U72.4 (-)
unnamed: C313.1, R524.2, U71.7
unnamed: C313.2, R525.1, R526.2, U71.6 (-)
unnamed: C314.1, R528.2, U71.8
unnamed: C314.2, Q153.2 (S), R530.1, R531.2, U71.9 (-)
unnamed: C315.2, R531.1, R532.2
unnamed: C316.1, R532.1, U71.12 (+)
unnamed: C317.1, D62.1 (K), Q154.3 (D), R535.1, U73.3 (+)
unnamed: C318.1, R537.2, U73.1
unnamed: C318.2, Q155.2 (S), R536.1, U73.2 (-)
unnamed: C322.1, R540.2, U74.1
unnamed: C322.2, Q156.3 (S), R544.2, U73.10 (+), U74.4 (-)
unnamed: C323.1, R541.2, U73.7
unnamed: C323.2, R542.1, R543.2, U73.6 (-)
unnamed: C324.1, R545.2, U73.8
unnamed: C324.2, Q158.2 (S), R547.1, R548.2, U73.9 (-)
unnamed: C325.2, R548.1, R549.2
unnamed: C326.1, R549.1, U73.12 (+)
unnamed: C328.1, D63.1 (K), Q161.3 (D), R558.1, U76.3 (+)
unnamed: C329.1, R560.2, U76.1
unnamed: C329.2, Q162.2 (S), R559.1, U76.2 (-)
unnamed: C333.1, R563.2, U77.1
unnamed: C333.2, Q163.3 (S), R567.2, U76.10 (+), U77.4 (-)
unnamed: C334.1, R564.2, U76.7
unnamed: C334.2, R565.1, R566.2, U76.6 (-)
unnamed: C335.1, R568.2, U76.8
unnamed: C335.2, Q165.2 (S), R570.1, R571.2, U76.9 (-)
unnamed: C336.2, R571.1, R572.2
unnamed: C337.1, R572.1, U76.12 (+)
unnamed: C338.1, D64.1 (K), Q166.3 (D), R575.1, U78.3 (+)
unnamed: C339.1, R577.2, U78.1
unnamed: C339.2, Q167.2 (S), R576.1, U78.2 (-)
unnamed: C343.1, R580.2, U79.1
unnamed: C343.2, Q168.3 (S), R584.2, U78.10 (+), U79.4 (-)
unnamed: C344.1, R581.2, U78.7
unnamed: C344.2, R582.1, R583.2, U78.6 (-)
unnamed: C345.1, R585.2, U78.8
unnamed: C345.2, Q170.2 (S), R587.1, R588.2, U78.9 (-)
unnamed: C346.2, R588.1, R589.2
unnamed: C347.1, R589.1, U78.12 (+)
unnamed: C349.1, D65.1 (K), Q173.3 (D), R598.1, U81.3 (+)
unnamed: C350.1, R600.2, U81.1
unnamed: C350.2, Q174.2 (S), R599.1, U81.2 (-)
unnamed: C354.1, R603.2, U82.1
unnamed: C354.2, Q175.3 (S), R607.2, U81.10 (+), U82.4 (-)
unnamed: C355.1, R604.2, U81.7
unnamed: C355.2, R605.1, R606.2, U81.6 (-)
unnamed: C356.1, R608.2, U81.8
unnamed: C356.2, Q177.2 (S), R610.1, R611.2, U81.9 (-)
unnamed: C357.2, R611.1, R612.2
unnamed: C358.1, R612.1, U81.12 (+)
unnamed: C359.1, D66.1 (K), Q178.3 (D), R615.1, U83.3 (+)
unnamed: C360.1, R617.2, U83.1
unnamed: C360.2, Q179.2 (S), R616.1, U83.2 (-)
unnamed: C364.1, R620.2, U84.1
unnamed: C364.2, Q180.3 (S), R624.2, U83.10 (+), U84.4 (-)
unnamed: C365.1, R621.2, U83.7
unnamed: C365.2, R622.1, R623.2, U83.6 (-)
unnamed: C366.1, R625.2, U83.8
unnamed: C366.2, Q182.2 (S), R627.1, R628.2, U83.9 (-)
unnamed: C367.2, R628.1, R629.2
unnamed: C368.1, R629.1, U83.12 (+)
unnamed: Q3.1 (G), R7.2, R8.1
unnamed: Q4.1 (G), R11.1
unnamed: Q4.3 (D), R13.2, U3.3 (+)
unnamed: Q5.1 (G), R14.1
unnamed: Q5.2 (D), Q6.2 (D)
unnamed: Q6.1 (G), R15.1
unnamed: Q7.1 (G), R19.1
unnamed: Q7.3 (D), R20.2
unnamed: Q16.1 (G), R59.2, R60.1
unnamed: Q17.1 (G), R63.1
unnamed: Q17.3 (D), R65.2, U12.3 (+)
unnamed: Q18.1 (G), R66.1
unnamed: Q18.2 (D), Q19.2 (D)
unnamed: Q19.1 (G), R67.1
unnamed: Q20.1 (G), R71.1
unnamed: Q20.3 (D), R72.2
unnamed: Q21.1 (G), R76.2, R77.1
unnamed: Q22.1 (G), R80.1
unnamed: Q22.3 (D), R82.2, U14.3 (+)
unnamed: Q23.1 (G), R83.1
unnamed: Q23.2 (D), Q24.2 (D)
unnamed: Q24.1 (G), R84.1
unnamed: Q25.1 (G), R88.1
unnamed: Q25.3 (D), R89.2
unnamed: Q29.1 (G), R106.2, R107.1
unnamed: Q30.1 (G), R120.1
unnamed: Q30.3 (D), R122.2, U18.3 (+)
unnamed: Q31.1 (G), R123.1
unnamed: Q31.2 (D), Q32.2 (D)
unnamed: Q32.1 (G), R124.1
unnamed: Q33.1 (G), R128.1
unnamed: Q33.3 (D), R129.2
unnamed: Q34.1 (G), R133.2, R134.1
unnamed: Q35.1 (G), R137.1
unnamed: Q35.3 (D), R139.2, U24.3 (+)
unnamed: Q36.1 (G), R140.1
unnamed: Q36.2 (D), Q37.2 (D)
unnamed: Q37.1 (G), R141.1
unnamed: Q38.1 (G), R145.1
unnamed: Q38.3 (D), R146.2
unnamed: Q41.1 (G), R156.2, R157.1
unnamed: Q42.1 (G), R160.1
unnamed: Q42.3 (D), R162.2, U27.3 (+)
unnamed: Q43.1 (G), R163.1
unnamed: Q43.2 (D), Q44.2 (D)
unnamed: Q44.1 (G), R164.1
unnamed: Q45.1 (G), R168.1
unnamed: Q45.3 (D), R169.2
unnamed: Q46.1 (G), R173.2, R174.1
unnamed: Q47.1 (G), R177.1
unnamed: Q47.3 (D), R179.2, U29.3 (+)
unnamed: Q48.1 (G), R180.1
unnamed: Q48.2 (D), Q49.2 (D)
unnamed: Q49.1 (G), R181.1
unnamed: Q50.1 (G), R185.1
unnamed: Q50.3 (D), R186.2
unnamed: Q53.1 (G), R196.2, R197.1
unnamed: Q54.1 (G), R200.1
unnamed: Q54.3 (D), R202.2, U32.3 (+)
unnamed: Q55.1 (G), R203.1
unnamed: Q55.2 (D), Q56.2 (D)
unnamed: Q56.1 (G), R204.1
unnamed: Q57.1 (G), R208.1
unnamed: Q57.3 (D), R209.2
unnamed: Q58.1 (G), R213.2, R214.1
unnamed: Q59.1 (G), R217.1
unnamed: Q59.3 (D), R219.2, U34.3 (+)
unnamed: Q60.1 (G), R220.1
unnamed: Q60.2 (D), Q61.2 (D)
unnamed: Q61.1 (G), R221.1
unnamed: Q62.1 (G), R225.1
unnamed: Q62.3 (D), R226.2
unnamed: Q65.1 (G), R236.2, R237.1
unnamed: Q66.1 (G), R240.1
unnamed: Q66.3 (D), R242.2, U37.3 (+)
unnamed: Q67.1 (G), R243.1
unnamed: Q67.2 (D), Q68.2 (D)
unnamed: Q68.1 (G), R244.1
unnamed: Q69.1 (G), R248.1
unnamed: Q69.3 (D), R249.2
unnamed: Q70.1 (G), R253.2, R254.1
unnamed: Q71.1 (G), R257.1
unnamed: Q71.3 (D), R259.2, U39.3 (+)
unnamed: Q72.1 (G), R260.1
unnamed: Q72.2 (D), Q73.2 (D)
unnamed: Q73.1 (G), R261.1
unnamed: Q74.1 (G), R265.1
unnamed: Q74.3 (D), R266.2
unnamed: Q77.1 (G), R276.2, R277.1
unnamed: Q78.1 (G), R280.1
unnamed: Q78.3 (D), R282.2, U42.3 (+)
unnamed: Q79.1 (G), R283.1
unnamed: Q79.2 (D), Q80.2 (D)
unnamed: Q80.1 (G), R284.1
unnamed: Q81.1 (G), R288.1
unnamed: Q81.3 (D), R289.2
unnamed: Q82.1 (G), R293.2, R294.1
unnamed: Q83.1 (G), R297.1
unnamed: Q83.3 (D), R299.2, U44.3 (+)
unnamed: Q84.1 (G), R300.1
unnamed: Q84.2 (D), Q85.2 (D)
unnamed: Q85.1 (G), R301.1
unnamed: Q86.1 (G), R305.1
unnamed: Q86.3 (D), R306.2
unnamed: Q89.1 (G), R316.2, R317.1
unnamed: Q90.1 (G), R320.1
unnamed: Q90.3 (D), R322.2, U47.3 (+)
unnamed: Q91.1 (G), R323.1
unnamed: Q91.2 (D), Q92.2 (D)
unnamed: Q92.1 (G), R324.1
unnamed: Q93.1 (G), R328.1
unnamed: Q93.3 (D), R329.2
unnamed: Q94.1 (G), R333.2, R334.1
unnamed: Q95.1 (G), R337.1
unnamed: Q95.3 (D), R339.2, U49.3 (+)
unnamed: Q96.1 (G), R340.1
unnamed: Q96.2 (D), Q97.2 (D)
unnamed: Q97.1 (G), R341.1
unnamed: Q98.1 (G), R345.1
unnamed: Q98.3 (D), R346.2
unnamed: Q101.1 (G), R356.2, R357.1
unnamed: Q102.1 (G), R360.1
unnamed: Q102.3 (D), R362.2, U52.3 (+)
unnamed: Q103.1 (G), R363.1
unnamed: Q103.2 (D), Q104.2 (D)
unnamed: Q104.1 (G), R364.1
unnamed: Q105.1 (G), R368.1
unnamed: Q105.3 (D), R369.2
unnamed: Q106.1 (G), R373.2, R374.1
unnamed: Q107.1 (G), R377.1
unnamed: Q107.3 (D), R379.2, U54.3 (+)
unnamed: Q108.1 (G), R380.1
unnamed: Q108.2 (D), Q109.2 (D)
unnamed: Q109.1 (G), R381.1
unnamed: Q110.1 (G), R385.1
unnamed: Q110.3 (D), R386.2
unnamed: Q113.1 (G), R396.2, R397.1
unnamed: Q114.1 (G), R400.1
unnamed: Q114.3 (D), R402.2, U57.3 (+)
unnamed: Q115.1 (G), R403.1
unnamed: Q115.2 (D), Q116.2 (D)
unnamed: Q116.1 (G), R404.1
unnamed: Q117.1 (G), R408.1
unnamed: Q117.3 (D), R409.2
unnamed: Q118.1 (G), R413.2, R414.1
unnamed: Q119.1 (G), R417.1
unnamed: Q119.3 (D), R419.2, U59.3 (+)
unnamed: Q120.1 (G), R420.1
unnamed: Q120.2 (D), Q121.2 (D)
unnamed: Q121.1 (G), R421.1
unnamed: Q122.1 (G), R425.1
unnamed: Q122.3 (D), R426.2
unnamed: Q125.1 (G), R436.2, R437.1
unnamed: Q126.1 (G), R440.1
unnamed: Q126.3 (D), R442.2, U62.3 (+)
unnamed: Q127.1 (G), R443.1
unnamed: Q127.2 (D), Q128.2 (D)
unnamed: Q128.1 (G), R444.1
unnamed: Q129.1 (G), R448.1
unnamed: Q129.3 (D), R449.2
unnamed: Q130.1 (G), R453.2, R454.1
unnamed: Q131.1 (G), R457.1
unnamed: Q131.3 (D), R459.2, U64.3 (+)
unnamed: Q132.1 (G), R460.1
unnamed: Q132.2 (D), Q133.2 (D)
unnamed: Q133.1 (G), R461.1
unnamed: Q134.1 (G), R465.1
unnamed: Q134.3 (D), R466.2
unnamed: Q137.1 (G), R476.2, R477.1
unnamed: Q138.1 (G), R480.1
unnamed: Q138.3 (D), R482.2, U67.3 (+)
unnamed: Q139.1 (G), R483.1
unnamed: Q139.2 (D), Q140.2 (D)
unnamed: Q140.1 (G), R484.1
unnamed: Q141.1 (G), R488.1
unnamed: Q141.3 (D), R489.2
unnamed: Q142.1 (G), R493.2, R494.1
unnamed: Q143.1 (G), R497.1
unnamed: Q143.3 (D), R499.2, U69.3 (+)
unnamed: Q144.1 (G), R500.1
unnamed: Q144.2 (D), Q145.2 (D)
unnamed: Q145.1 (G), R501.1
unnamed: Q146.1 (G), R505.1
unnamed: Q146.3 (D), R506.2
unnamed: Q149.1 (G), R516.2, R517.1
unnamed: Q150.1 (G), R520.1
unnamed: Q150.3 (D), R522.2, U72.3 (+)
unnamed: Q151.1 (G), R523.1
unnamed: Q151.2 (D), Q152.2 (D)
unnamed: Q152.1 (G), R524.1
unnamed: Q153.1 (G), R528.1
unnamed: Q153.3 (D), R529.2
unnamed: Q154.1 (G), R533.2, R534.1
unnamed: Q155.1 (G), R537.1
unnamed: Q155.3 (D), R539.2, U74.3 (+)
unnamed: Q156.1 (G), R540.1
unnamed: Q156.2 (D), Q157.2 (D)
unnamed: Q157.1 (G), R541.1
unnamed: Q158.1 (G), R545.1
unnamed: Q158.3 (D), R546.2
unnamed: Q161.1 (G), R556.2, R557.1
unnamed: Q162.1 (G), R560.1
unnamed: Q162.3 (D), R562.2, U77.3 (+)
unnamed: Q163.1 (G), R563.1
unnamed: Q163.2 (D), Q164.2 (D)
unnamed: Q164.1 (G), R564.1
unnamed: Q165.1 (G), R568.1
unnamed: Q165.3 (D), R569.2
unnamed: Q166.1 (G), R573.2, R574.1
unnamed: Q167.1 (G), R577.1
unnamed: Q167.3 (D), R579.2, U79.3 (+)
unnamed: Q168.1 (G), R580.1
unnamed: Q168.2 (D), Q169.2 (D)
unnamed: Q169.1 (G), R581.1
unnamed: Q170.1 (G), R585.1
unnamed: Q170.3 (D), R586.2
unnamed: Q173.1 (G), R596.2, R597.1
unnamed: Q174.1 (G), R600.1
unnamed: Q174.3 (D), R602.2, U82.3 (+)
unnamed: Q175.1 (G), R603.1
unnamed: Q175.2 (D), Q176.2 (D)
unnamed: Q176.1 (G), R604.1
unnamed: Q177.1 (G), R608.1
unnamed: Q177.3 (D), R609.2
unnamed: Q178.1 (G), R613.2, R614.1
unnamed: Q179.1 (G), R617.1
unnamed: Q179.3 (D), R619.2, U84.3 (+)
unnamed: Q180.1 (G), R620.1
unnamed: Q180.2 (D), Q181.2 (D)
unnamed: Q181.1 (G), R621.1
unnamed: Q182.1 (G), R625.1
unnamed: Q182.3 (D), R626.2
